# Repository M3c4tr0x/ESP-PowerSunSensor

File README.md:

# Irradiance and Theoretical Power Calculation Board for Photovoltaic Systems

This board is designed to measure irradiance using a small solar panel and to estimate the theoretical power output of a photovoltaic installation using an NTC temperature sensor placed on one of the panels.

The system is intended for photovoltaic setups that **cannot inject electricity into the grid** — whether on-grid or off-grid. It helps determine real-time production capacity and supports better energy management and self-consumption.

## Features

- **Irradiance Measurement**  
  A miniature solar panel captures real-time irradiance levels.

- **Theoretical Power Estimation**  
  An NTC sensor measures panel temperature to calculate expected power output under current conditions.

- **No-Grid-Injection Systems**  
  Ideal for photovoltaic installations restricted from injecting power into the grid.

- **Performance Monitoring**  
  Provides data to evaluate the system's efficiency and optimize energy usage.
  
  On the first graphe below, you can see the values of the ESP-PowerSunSensor are shown in blue, and my solar production values in yellow :

  Below is the list of the different data reported by the sensor : 

## Use Cases

- Estimating maximum potential production of a solar installation  
- Monitoring performance over time  
- Supporting system design or troubleshooting  
- Managing loads in self-consumption scenarios

## Required Components

- Miniature solar panel (I personally used the glass solar panel from a solar garden lamp recovered from the recycling center)  
- NTC temperature sensor (attach to one of the main panels) : Any NTC sensor can be used, as long as you adapt the pull-up resistor (R16 on the PCB) value and know the sensor’s B25/50 characteristics, which should be entered into the YAML configuration.
- An ESP-PowerSunSensor PCB wired according to the associated schematic diagram
- Power supply and data interface (USB, Wi-Fi, etc.)

Beta version : 

## 💰 How Much Does It Cost?

This project is designed to be **as low-cost as possible**, using affordable or recycled components.

| Component                        | Estimated Price (€) | Notes                                                                 |
|----------------------------------|----------------------|-----------------------------------------------------------------------|
| Miniature solar panel            | 0 – 5 €              | Recovered from a solar garden lamp (recycling center, old devices)   |
| NTC temperature sensor           | 1 – 3 €              | Any NTC sensor works 10kR to 100kR (adapt pull-up resistor and B-value in YAML)    |
| ESP32-C3-WROOM-02                | 3 – 8 €              |                                                                      |
| ESP-PowerSunSensor PCB           | 2 – 5 €              | Depending on quantity and supplier (JLCPCB, PCBWay, etc.)            |
| Resistors, connectors, etc.      | 1 – 2 €              | Very cheap, or reusable from old electronics                         |
| 5V USB power supply              | 2 – 5 €              | Standard USB charger or reused power source                          |

### 💡 Total Estimated Cost: **around 10 to 25 €**

> 💬 **Tip**: If you recycle parts (panel, power supply, cables), the full setup can cost **less than 10 €**!

## Installation

1. Connect J2 by strapping it to enable bootloader mode on the ESP32
2. Attach the electronic board to your computer using an USB cable.
3. Disconnect J2 (unstrap it) after enabling bootloader mode
4. Go to your ESP-home server and flash the new device with attached yaml customized for your settings
5. After that, you can remove the USB cable
6. Connect the miniature solar panel to the input for irradiance measurement (J3).
7. Attach the NTC sensor firmly to the back side of one of your main solar panels and connect it on J1 connector.

8. Mount the sensor in same direction of your installation you want to monitor, example (files attached in repo) :

9. You can separate the solar panel and NTC sensor from the electronics PCB. In my case, they are positioned 15 meters apart, and the system works fine. This tip allows for a better Wi-Fi connection by placing the electronics closer to my Wi-Fi access point.
10. Connect the USB cable to the power supply.
11. Enjoy your setup and power monitoring!

## Author

- @M3c4tr0x

## License

[MIT License]

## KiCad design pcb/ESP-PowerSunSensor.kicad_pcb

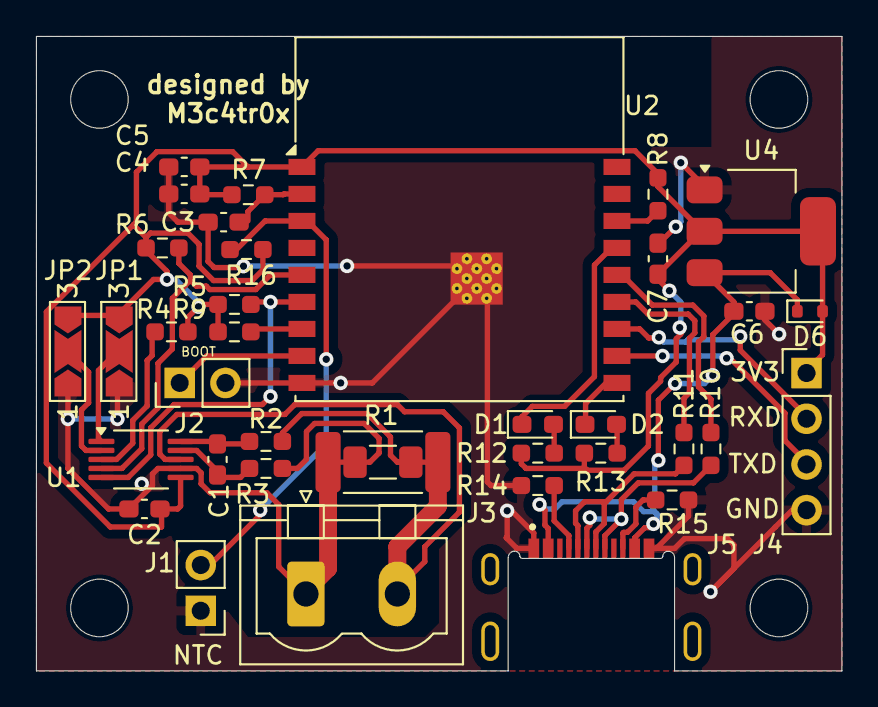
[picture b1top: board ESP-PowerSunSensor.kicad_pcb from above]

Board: 2 copper layers, 44.8 x 35.2 mm, 40 parts (0 on the bottom side), 28 nets.

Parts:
C1: 220nF; C_0603_1608Metric_Pad1.08x0.95mm_HandSolder
C2, C3, C5: 100nF; C_0603_1608Metric_Pad1.08x0.95mm_HandSolder
C4, C6, C7: 10uF; C_0603_1608Metric_Pad1.08x0.95mm_HandSolder
D1, D2: LED; LED_0603_1608Metric_Pad1.05x0.95mm_HandSolder
D6: BAS516; D_SOD-523
FID1, FID2, FID3, FID4: Fiducial; MountingHole_3.2mm_M3
J1, J2: Conn_01x02_Pin; PinHeader_1x02_P2.54mm_Vertical
J3: Conn_01x02; PhoenixContact_MSTBVA_2,5_2-G-5,08_1x02_P5.08mm_Vertical
J4: Conn_01x04_Pin; PinHeader_1x04_P2.54mm_Vertical
J5: USB_C_Receptacle_USB2.0_16P; GCT_USB4500-03-0-A_REVA1
JP1, JP2: SolderJumper_3_Open; SolderJumper-3_P2.0mm_Open_TrianglePad1.0x1.5mm_NumberLabels
R1: R; R_2512_6332Metric_Pad1.40x3.35mm_HandSolder
R2, R3: 10R; R_0603_1608Metric_Pad0.98x0.95mm_HandSolder
R4, R5, R6, R7, R8, R9: 10k; R_0603_1608Metric_Pad0.98x0.95mm_HandSolder
R10, R11: 0R; R_0603_1608Metric_Pad0.98x0.95mm_HandSolder
R12, R13, R16: 1k; R_0603_1608Metric_Pad0.98x0.95mm_HandSolder
R14, R15: 5.1k; R_0603_1608Metric_Pad0.98x0.95mm_HandSolder
U1: INA228; VSSOP-10_3x3mm_P0.5mm
U2: ESP32-C3-WROOM-02
U4: NCP1117-3.3_SOT223; SOT-223-3_TabPin2

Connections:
+3V3: C2.1, C4.1, C5.1, C7.1, D6.2 (A), J4.1, JP1.3 (B), JP2.3 (B), R4.1, R5.1, R6.1, R7.1, R8.1, R9.1, R12.1, R13.1, R16.1, U1.6 (VS), U2.1 (3V3), U4.2 (VO)
GND: C2.2, C3.2, C4.2, C5.2, C6.2, C7.2, J1.1, J2.2, J3.1, J4.4, J5.A1 (GND), J5.B1 (GND), JP1.1 (A), JP2.1 (A), R1.2, R3.1, R14.2, R15.2, U1.7 (GND), U2.9 (GND), U2.19 (GND), U4.1 (GND)
unnamed: D1.2 (A), R12.2
unnamed: D1.1 (K), U2.15 (IO3)
unnamed: D2.2 (A), R13.2
unnamed: D2.1 (K), U2.10 (IO10)
unnamed: C6.1, D6.1 (K), J5.A4 (VBUS), J5.B4 (VBUS), U4.3 (VI)
unnamed: J1.2, R16.2, U2.3 (IO4)
unnamed: J2.1, U2.8 (IO9)
unnamed: J3.2, R1.1, R2.1, U1.8 (Vbus)
unnamed: J4.2, U2.12 (IO21/TXD)
unnamed: J4.3, U2.11 (IO20/RXD)
unnamed: J5.A5 (CC1), R14.1
unnamed: J5.B5 (CC2), R15.1
unnamed: JP1.2 (C), U1.1 (A1)
unnamed: JP2.2 (C), U1.2 (A0)
unnamed: R5.2, U1.5 (SCL), U2.6 (IO7)
unnamed: R6.2, U1.4 (SDA), U2.5 (IO6)
unnamed: C1.1, R2.2, U1.10 (Vin+)
unnamed: C1.2, R3.2, U1.9 (Vin-)
unnamed: R4.2, U1.3 (~Alert)
unnamed: C3.1, R7.2, U2.2 (EN)
unnamed: R8.2, U2.16 (IO2)
unnamed: R9.2, U2.7 (IO8)
unnamed: R11.2, U2.13 (IO18)
unnamed: R10.2, U2.14 (IO19)
USB_D+: J5.A6 (D+), J5.B6 (D+), R10.1
USB_D-: J5.A7 (D-), J5.B7 (D-), R11.1

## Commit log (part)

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2025-10-15 First version
